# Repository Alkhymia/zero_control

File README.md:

# zero_control
zero_control

Blog post - https://facelesstech.wordpress.com/2019/01/05/zero-control/
Youtube - https://www.youtube.com/watch?v=EZkDTUuJNRs

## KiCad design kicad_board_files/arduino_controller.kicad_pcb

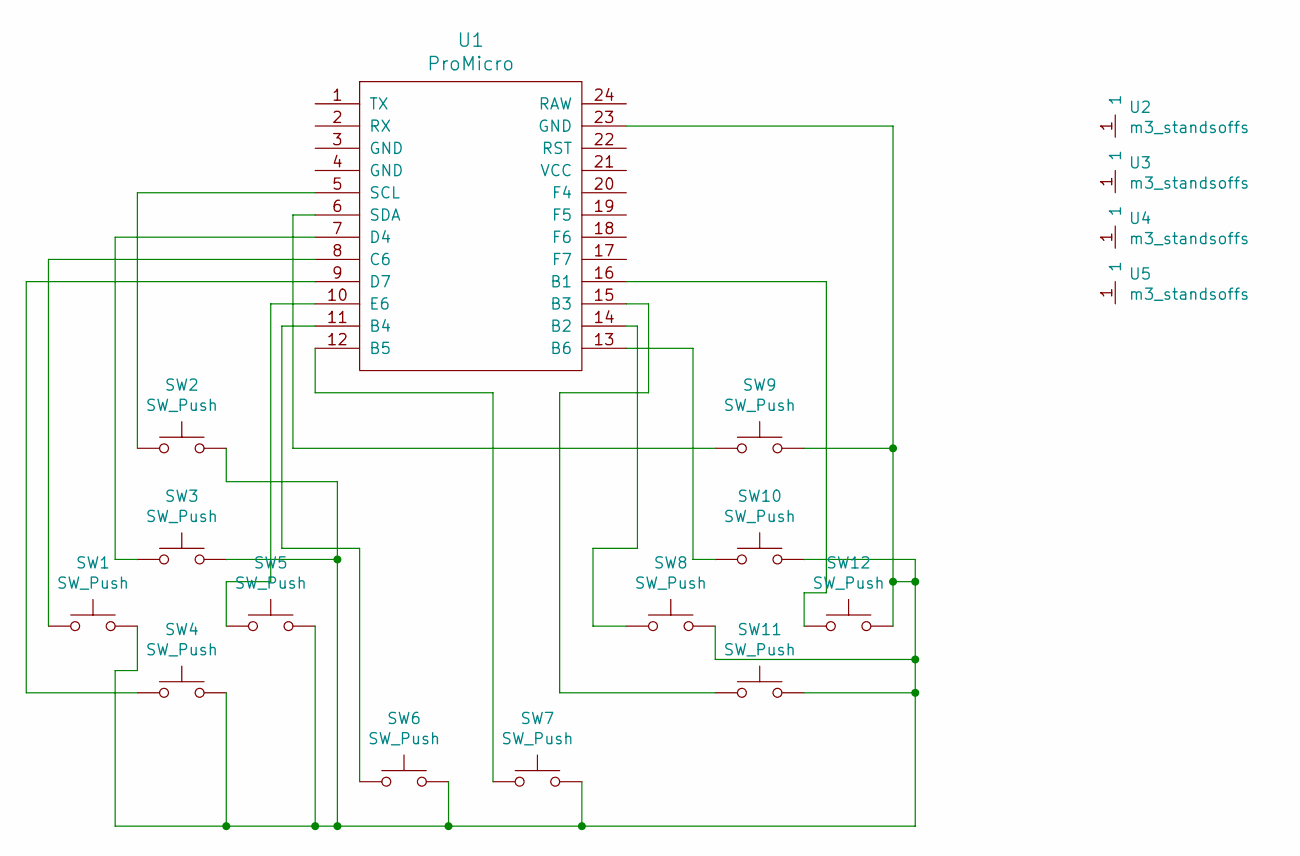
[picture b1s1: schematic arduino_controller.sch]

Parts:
SW1, SW2, SW3, SW4, SW5, SW6, SW7, SW8, SW9, SW10: SW_Push; smd_soft_custom
SW11, SW12: SW_Push; right_angle_2_pin
U1: ProMicro
U2, U3, U4, U5: m3_standsoffs; m3_hole_custom

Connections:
unnamed: SW1.1, U1.8 (C6)
unnamed: SW1.2, SW2.2, SW3.2, SW4.2, SW5.2, SW6.2, SW7.2, SW8.2, SW9.2, SW10.2, SW11.2, SW12.2, U1.23 (GND)
unnamed: SW2.1, U1.5 (SCL)
unnamed: SW3.1, U1.7 (D4)
unnamed: SW4.1, U1.9 (D7)
unnamed: SW5.1, U1.10 (E6)
unnamed: SW6.1, U1.11 (B4)
unnamed: SW7.1, U1.12 (B5)
unnamed: SW8.1, U1.14 (B2)
unnamed: SW9.1, U1.6 (SDA)
unnamed: SW10.1, U1.13 (B6)
unnamed: SW11.1, U1.15 (B3)
unnamed: SW12.1, U1.16 (B1)

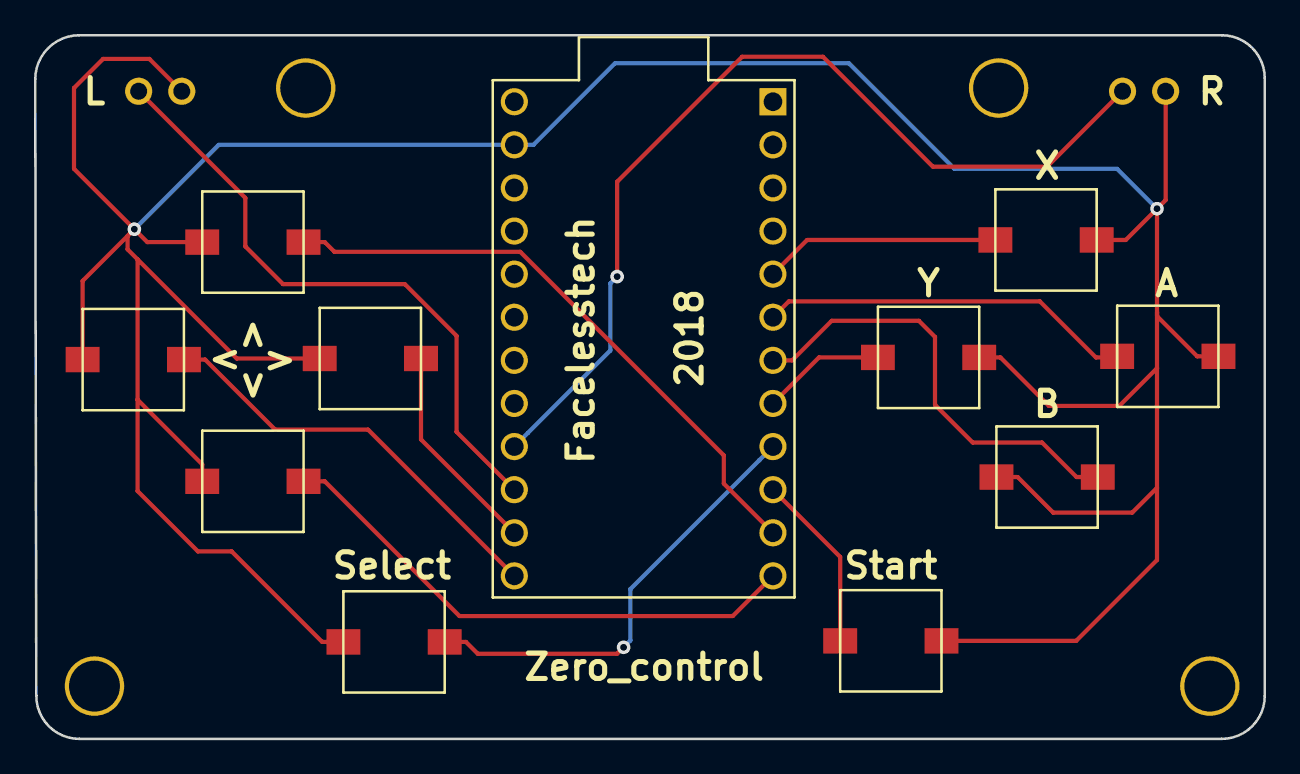
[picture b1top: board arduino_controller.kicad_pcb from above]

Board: 2 copper layers, 72.5 x 41.5 mm, 17 parts (1 on the bottom side), 13 nets.

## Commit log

2019-01-04 first upload
2019-01-04 board files for just the right angle buttons
2019-01-05 added links
